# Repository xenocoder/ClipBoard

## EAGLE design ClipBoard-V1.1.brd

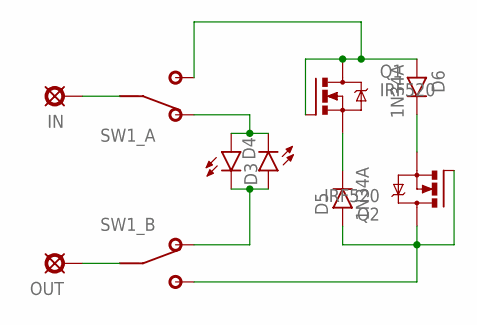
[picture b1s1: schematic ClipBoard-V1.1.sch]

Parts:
D3, D4: RED; LED3MM
D5, D6: 1N34A; DO07
IN: CLIPIN; SQUARE
OUT: CLIPOUT; SQUARE
Q1, Q2: IRF520; TO220BV
SW1: DPDT; DPDT_PCB

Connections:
unnamed: D3.K (C), D4.A, SW1.B2 (1)
unnamed: D5.C, Q1.S
unnamed: OUT.1, SW1.B1 (2)
unnamed: D6.C, Q2.S
unnamed: D6.A, Q1.D, Q1.G, SW1.A3 (3)
unnamed: IN.1, SW1.A1 (2)
unnamed: D3.A, D4.K (C), SW1.A2 (1)
unnamed: D5.A, Q2.D, Q2.G, SW1.B3 (3)

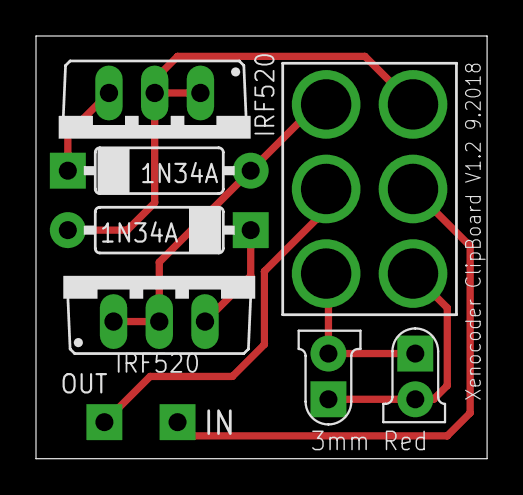
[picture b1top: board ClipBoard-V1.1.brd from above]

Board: 2 copper layers, 25.1 x 23.5 mm, 9 parts (0 on the bottom side), 8 nets.

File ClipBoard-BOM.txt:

Partlist exported from /Users/evanhowell/git/ClipBoard/ClipBoard-V1.1.sch at 10/18/18 6:25 PM

Part Value   Device     Package  Description         
D3   RED     LED3MM     LED3MM                       
D4   RED     LED3MM     LED3MM                       
D5   1N34A   DO07       DO07     DO-07 Package       
D6   1N34A   DO07       DO07     DO-07 Package       
IN   CLIPIN  PAD        SQUARE   PAD                 
OUT  CLIPOUT PAD        SQUARE   PAD                 
Q1   IRF520  IRF520     TO220BV  HEXFET Power MOSFET 
Q2   IRF520  IRF520     TO220BV  HEXFET Power MOSFET 
SW1  DPDT    DPDTDPDT_2 DPDT_PCB

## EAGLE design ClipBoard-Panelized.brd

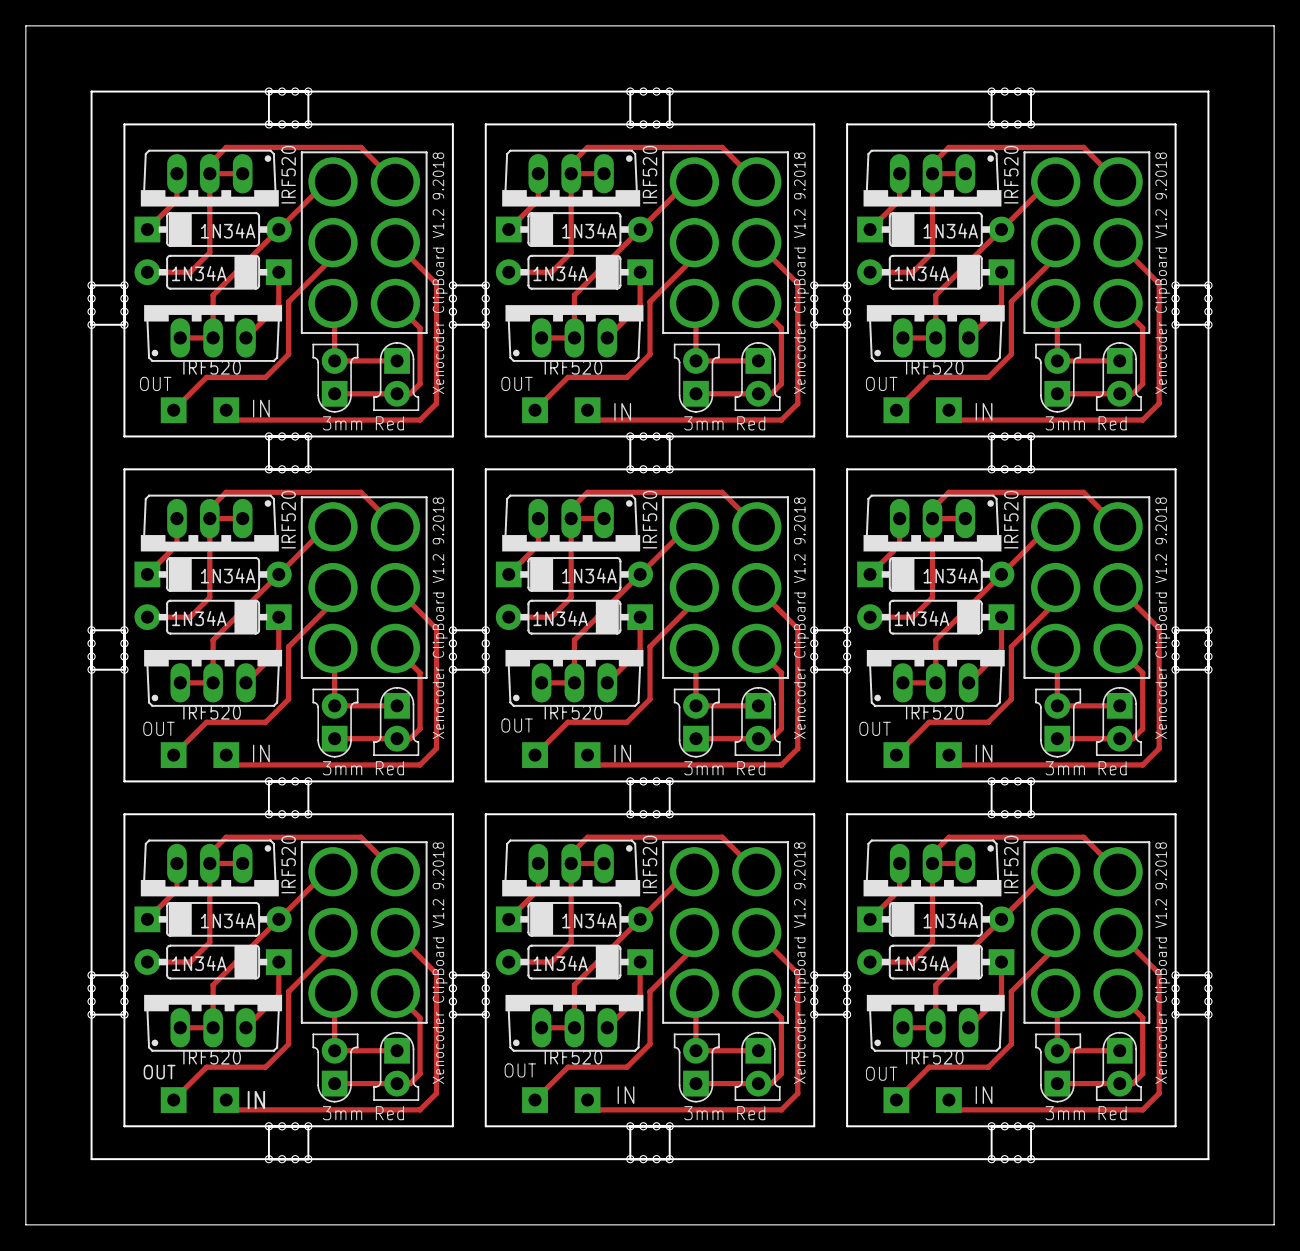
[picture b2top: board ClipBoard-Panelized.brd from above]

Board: 2 copper layers, 96.4 x 92.6 mm, 81 parts (0 on the bottom side), 72 nets.

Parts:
D1, D2, D3, D4, D9, D10, D13, D14, D17, D18, D21, D22, D25, D26, D29, D30, D33, D34: RED; LED3MM
D5, D6, D7, D8, D11, D12, D15, D16, D19, D20, D23, D24, D27, D28, D31, D32, D35, D36: 1N34A; DO07
IN, IN1, IN2, IN3, IN4, IN5, IN6, IN7, IN8: CLIPIN; SQUARE
OUT, OUT1, OUT2, OUT3, OUT4, OUT5, OUT6, OUT7, OUT8: CLIPOUT; SQUARE
Q1, Q2, Q3, Q4, Q5, Q6, Q7, Q8, Q9, Q10, Q11, Q12, Q13, Q14, Q15, Q16, Q17, Q18: IRF520; TO220BV
SW1, SW2, SW3, SW4, SW5, SW6, SW7, SW8, SW9: DPDT; DPDT_PCB

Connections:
unnamed: D3.K, D4.A, SW1.B2
unnamed: D5.C, Q1.S
unnamed: OUT.1, SW1.B1
unnamed: D6.C, Q2.S
unnamed: D6.A, Q1.D, Q1.G, SW1.A3
unnamed: IN.1, SW1.A1
unnamed: D3.A, D4.K, SW1.A2
unnamed: D5.A, Q2.D, Q2.G, SW1.B3
unnamed: D7.C, Q3.S
unnamed: D8.C, Q4.S
unnamed: D8.A, Q3.D, Q3.G, SW2.A3
unnamed: D1.A, D2.K, SW2.A2
unnamed: D7.A, Q4.D, Q4.G, SW2.B3
unnamed: D1.K, D2.A, SW2.B2
unnamed: IN1.1, SW2.A1
unnamed: OUT1.1, SW2.B1
unnamed: D11.C, Q5.S
unnamed: D12.C, Q6.S
unnamed: D12.A, Q5.D, Q5.G, SW3.A3
unnamed: D9.A, D10.K, SW3.A2
unnamed: D11.A, Q6.D, Q6.G, SW3.B3
unnamed: D9.K, D10.A, SW3.B2
unnamed: IN2.1, SW3.A1
unnamed: OUT2.1, SW3.B1
unnamed: D15.C, Q7.S
unnamed: D16.C, Q8.S
unnamed: D16.A, Q7.D, Q7.G, SW4.A3
unnamed: D13.A, D14.K, SW4.A2
unnamed: D15.A, Q8.D, Q8.G, SW4.B3
unnamed: D13.K, D14.A, SW4.B2
unnamed: IN3.1, SW4.A1
unnamed: OUT3.1, SW4.B1
unnamed: D19.C, Q9.S
unnamed: D20.C, Q10.S
unnamed: D20.A, Q9.D, Q9.G, SW5.A3
unnamed: D17.A, D18.K, SW5.A2
unnamed: D19.A, Q10.D, Q10.G, SW5.B3
unnamed: D17.K, D18.A, SW5.B2
unnamed: IN4.1, SW5.A1
unnamed: OUT4.1, SW5.B1
unnamed: D23.C, Q11.S
unnamed: D24.C, Q12.S
unnamed: D24.A, Q11.D, Q11.G, SW6.A3
unnamed: D21.A, D22.K, SW6.A2
unnamed: D23.A, Q12.D, Q12.G, SW6.B3
unnamed: D21.K, D22.A, SW6.B2
unnamed: IN5.1, SW6.A1
unnamed: OUT5.1, SW6.B1
unnamed: D27.C, Q13.S
unnamed: D28.C, Q14.S
unnamed: D28.A, Q13.D, Q13.G, SW7.A3
unnamed: D25.A, D26.K, SW7.A2
unnamed: D27.A, Q14.D, Q14.G, SW7.B3
unnamed: D25.K, D26.A, SW7.B2
unnamed: IN6.1, SW7.A1
unnamed: OUT6.1, SW7.B1
unnamed: D31.C, Q15.S
unnamed: D32.C, Q16.S
unnamed: D32.A, Q15.D, Q15.G, SW8.A3
unnamed: D29.A, D30.K, SW8.A2
unnamed: D31.A, Q16.D, Q16.G, SW8.B3
unnamed: D29.K, D30.A, SW8.B2
unnamed: IN7.1, SW8.A1
unnamed: OUT7.1, SW8.B1
unnamed: D35.C, Q17.S
unnamed: D36.C, Q18.S
unnamed: D36.A, Q17.D, Q17.G, SW9.A3
unnamed: D33.A, D34.K, SW9.A2
unnamed: D35.A, Q18.D, Q18.G, SW9.B3
unnamed: D33.K, D34.A, SW9.B2
unnamed: IN8.1, SW9.A1
unnamed: OUT8.1, SW9.B1

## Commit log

2018-09-30 First commit of board and panel
2018-10-19 Added Schematic and BOM
